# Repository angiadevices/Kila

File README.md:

**!!THIS IS CURRENTLY ENTIRELY UNTESTED!!**

**TODO:** Test PCB design.
Make a better PCB layout because this one is just a complete mess. But if it works...?

## Kila

Kila | किला: Fort/Castle

A Eurorack adaptation of the [Bastl Kastle](https://bastl-instruments.com/instruments/kastle).

This is almost entirely based specifically on the [Sluisbrinkie Kepler](https://github.com/niektb/sluisbrinkie-eurorack-published/tree/main/Sluisbrinkie%20Kepler). There were no hardware files available so I decided to venture into laying out my own.

14HP</br>
Eschews the switches of the original for purely potentiometers and mono jacks.</br>
Includes header for power via external +5VDC source.

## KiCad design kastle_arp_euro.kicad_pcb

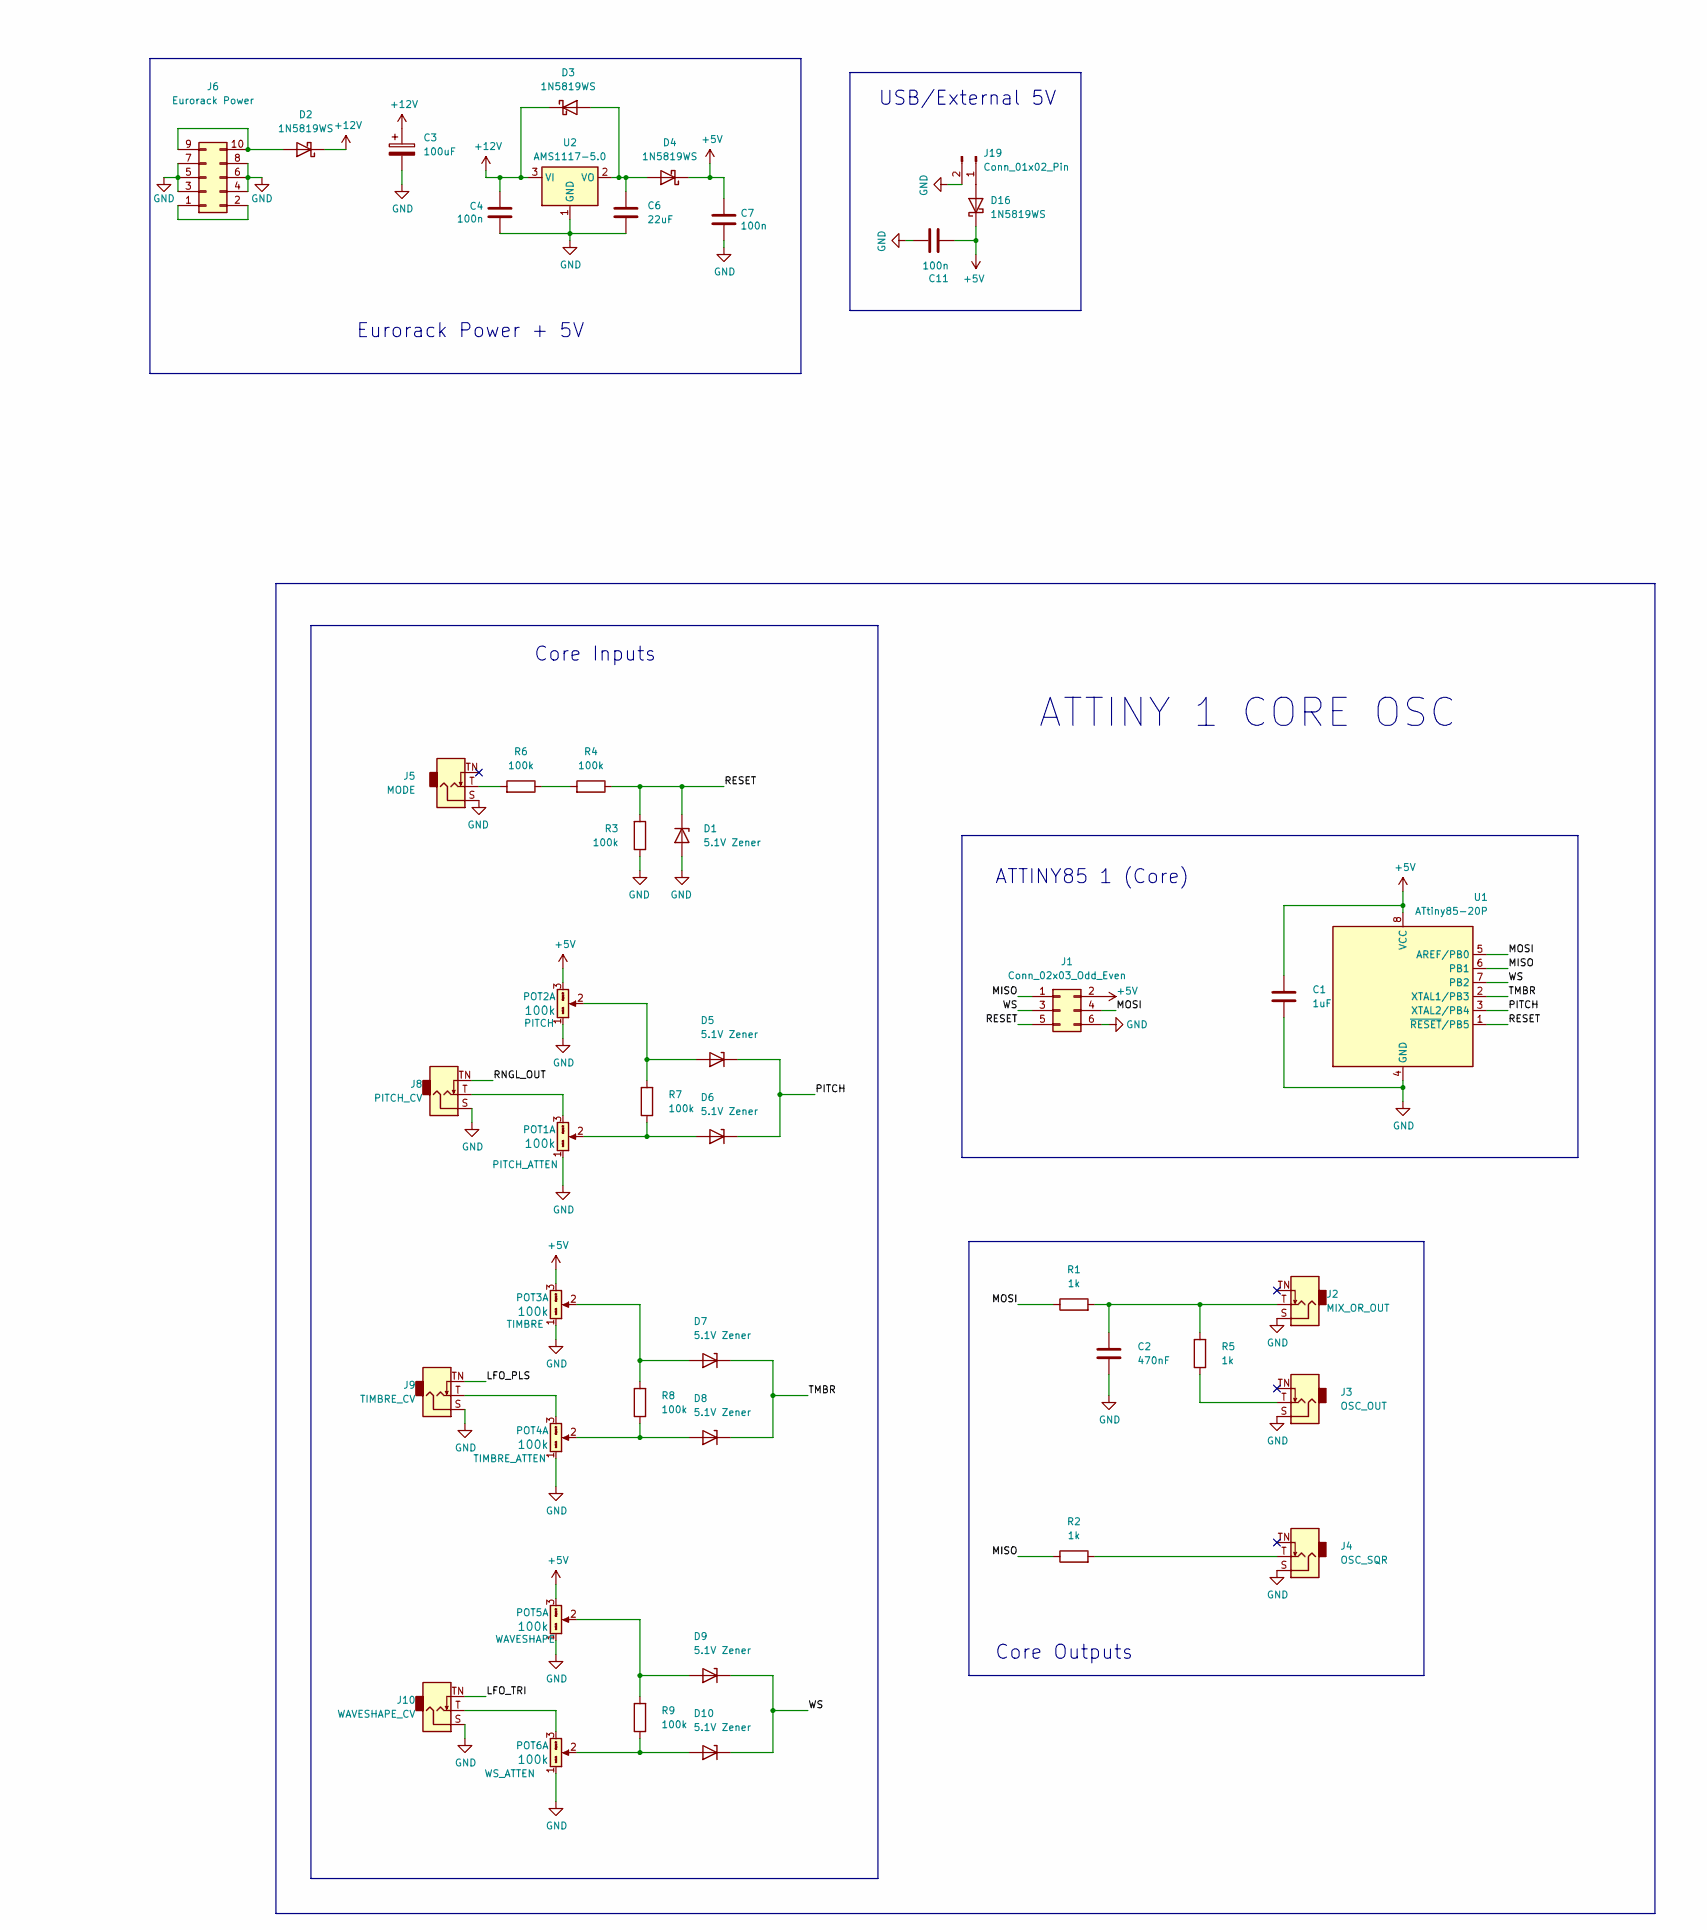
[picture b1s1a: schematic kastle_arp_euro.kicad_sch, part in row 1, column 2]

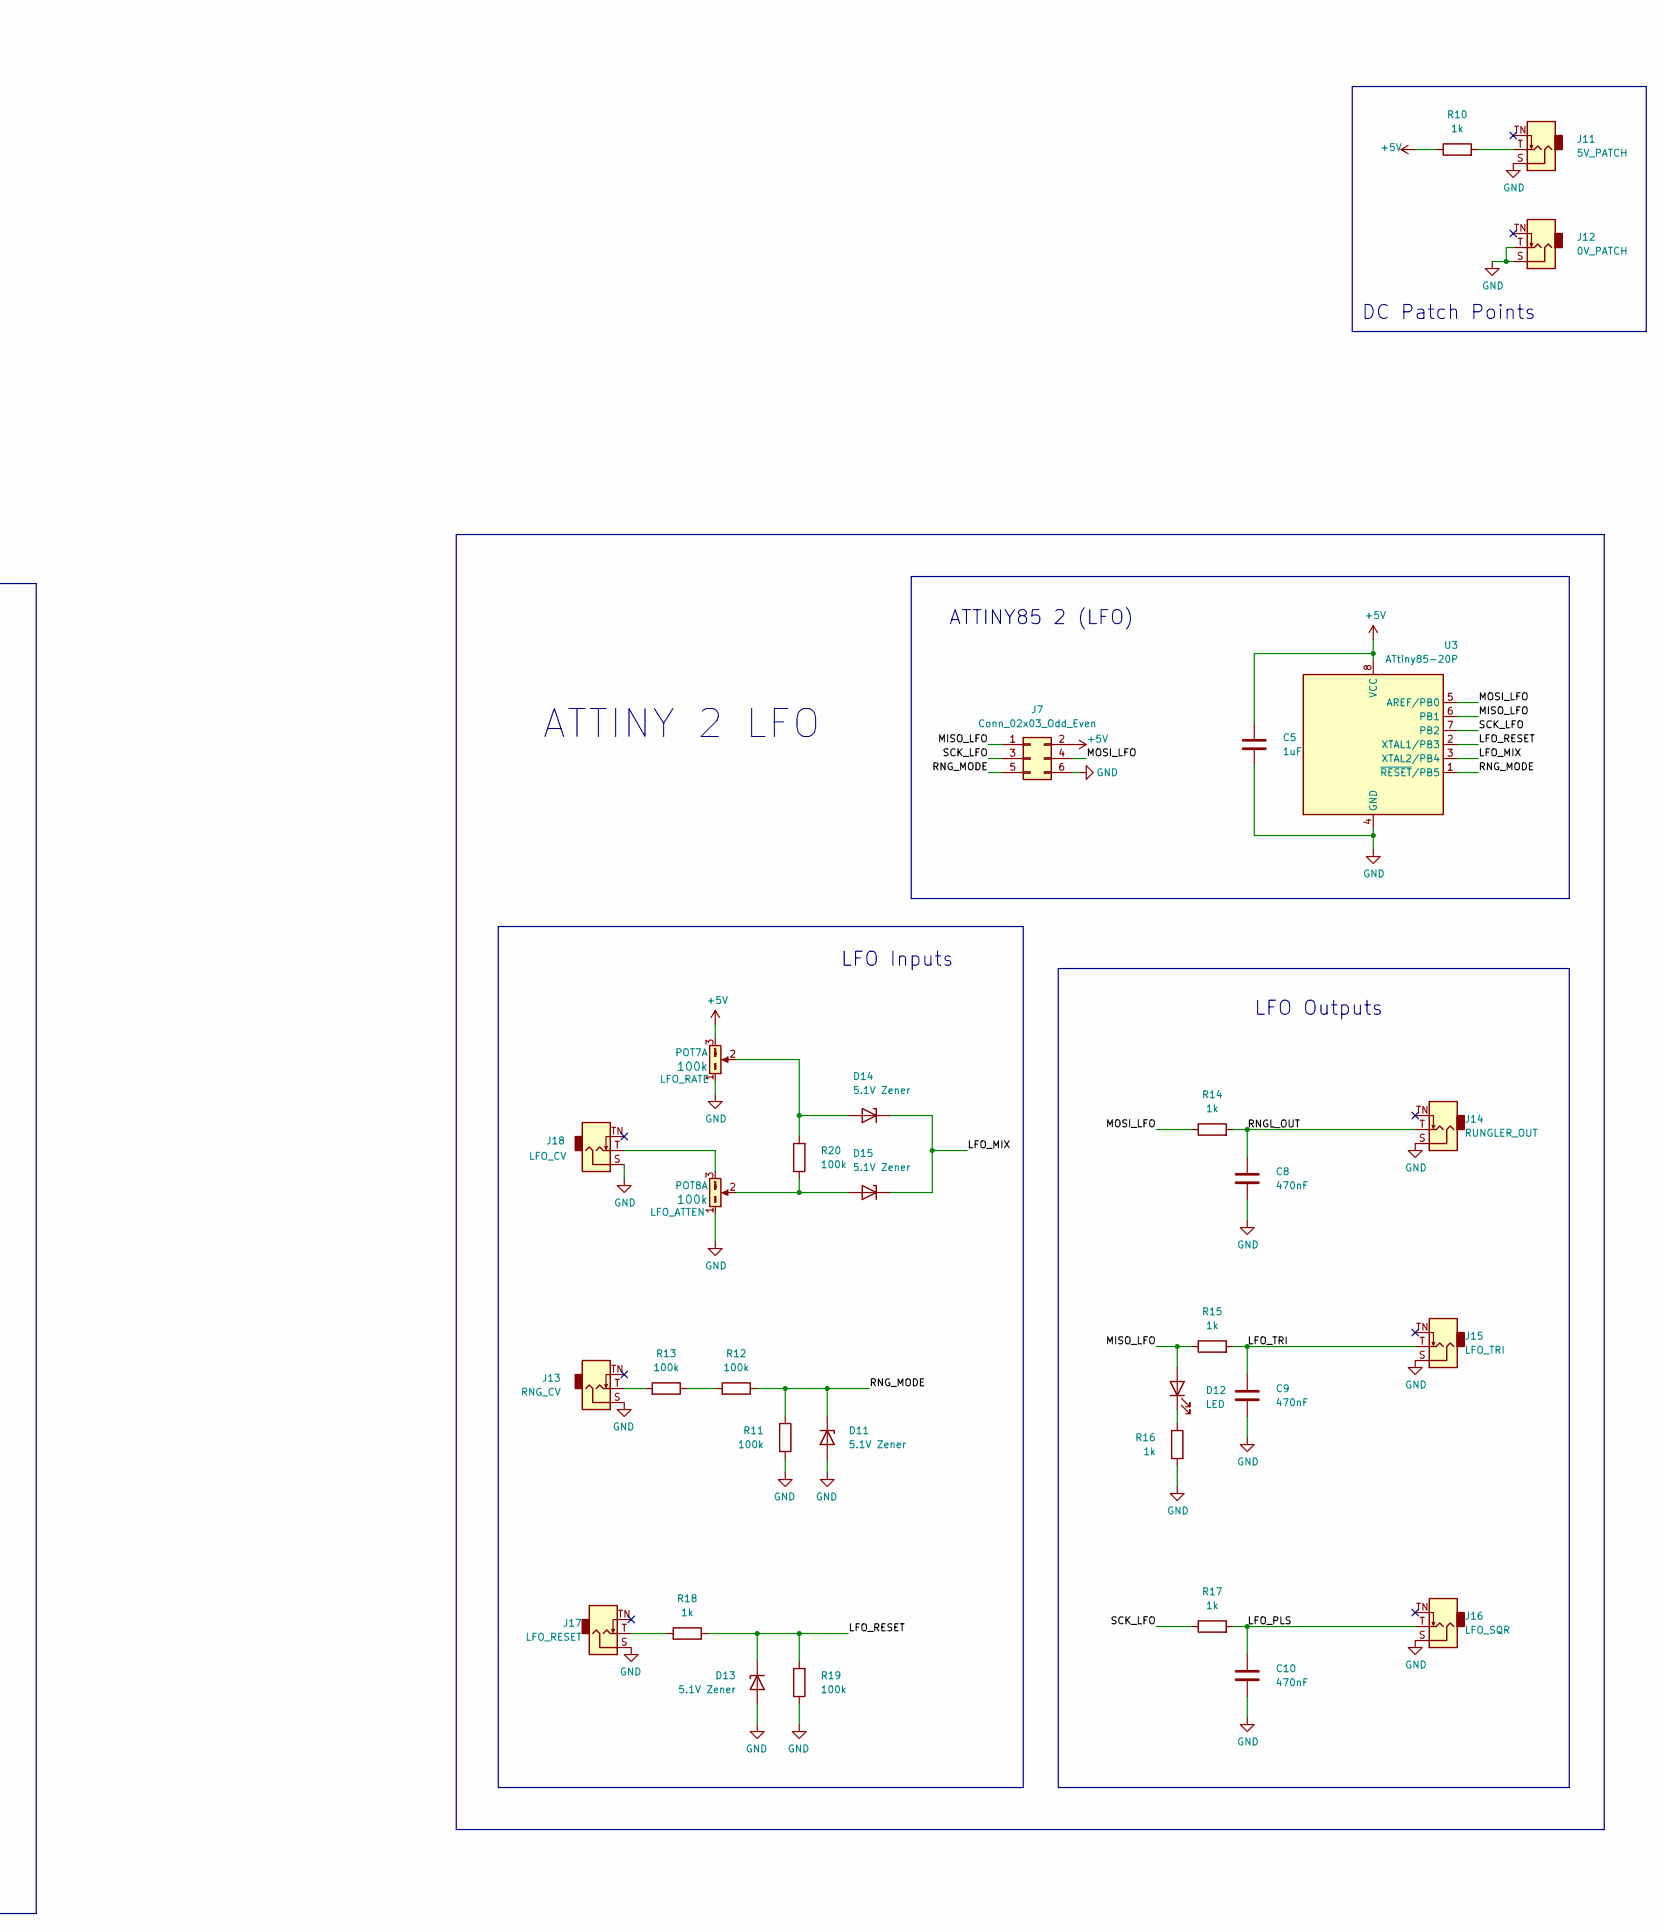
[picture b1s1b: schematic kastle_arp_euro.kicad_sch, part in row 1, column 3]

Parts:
C1, C5: 1uF; C_0805_2012Metric_Pad1.18x1.45mm_HandSolder
C2, C8, C9, C10: 470nF; C_0805_2012Metric_Pad1.18x1.45mm_HandSolder
C3: 100uF; CP_Radial_D6.3mm_P2.50mm
C4, C7, C11: 100n; C_0805_2012Metric_Pad1.18x1.45mm_HandSolder
C6: 22uF; C_1206_3216Metric_Pad1.33x1.80mm_HandSolder
D1, D5, D6, D7, D8, D9, D10, D11, D13, D14, D15: 5.1V Zener; D_MiniMELF_Handsoldering
D2, D3, D4, D16: 1N5819WS; D_SOD-323_HandSoldering
D12: LED; LED_D3.0mm
J1, J7: Conn_02x03_Odd_Even; PinHeader_2x03_P2.54mm_Vertical
J2: MIX_OR_OUT; Jack_3.5mm_QingPu_WQP-PJ398SM_Vertical_CircularHoles
J3: OSC_OUT; Jack_3.5mm_QingPu_WQP-PJ398SM_Vertical_CircularHoles
J4: OSC_SQR; Jack_3.5mm_QingPu_WQP-PJ398SM_Vertical_CircularHoles
J5: MODE; Jack_3.5mm_QingPu_WQP-PJ398SM_Vertical_CircularHoles
J6: Eurorack Power; IDC-Header_2x05_P2.54mm_Vertical
J8: PITCH_CV; Jack_3.5mm_QingPu_WQP-PJ398SM_Vertical_CircularHoles
J9: TIMBRE_CV; Jack_3.5mm_QingPu_WQP-PJ398SM_Vertical_CircularHoles
J10: WAVESHAPE_CV; Jack_3.5mm_QingPu_WQP-PJ398SM_Vertical_CircularHoles
J11: 5V_PATCH; Jack_3.5mm_QingPu_WQP-PJ398SM_Vertical_CircularHoles
J12: 0V_PATCH; Jack_3.5mm_QingPu_WQP-PJ398SM_Vertical_CircularHoles
J13: RNG_CV; Jack_3.5mm_QingPu_WQP-PJ398SM_Vertical_CircularHoles
J14: RUNGLER_OUT; Jack_3.5mm_QingPu_WQP-PJ398SM_Vertical_CircularHoles
J15: LFO_TRI; Jack_3.5mm_QingPu_WQP-PJ398SM_Vertical_CircularHoles
J16: LFO_SQR; Jack_3.5mm_QingPu_WQP-PJ398SM_Vertical_CircularHoles
J17: LFO_RESET; Jack_3.5mm_QingPu_WQP-PJ398SM_Vertical_CircularHoles
J18: LFO_CV; Jack_3.5mm_QingPu_WQP-PJ398SM_Vertical_CircularHoles
J19: Conn_01x02_Pin; JST_EH_B2B-EH-A_1x02_P2.50mm_Vertical
POT1: PITCH_ATTEN; Potentiometer_Alpha_RD901F-40-00D_Single_Vertical; Part Number RV16AF-4A-15FW-B100K-3
POT2: PITCH; Potentiometer_Alpha_RD901F-40-00D_Single_Vertical; Part Number RV16AF-4A-15FW-B100K-3
POT3: TIMBRE; Potentiometer_Alpha_RD901F-40-00D_Single_Vertical; Part Number RV16AF-4A-15FW-B100K-3
POT4: TIMBRE_ATTEN; Potentiometer_Alpha_RD901F-40-00D_Single_Vertical; Part Number RV16AF-4A-15FW-B100K-3
POT5: WAVESHAPE; Potentiometer_Alpha_RD901F-40-00D_Single_Vertical; Part Number RV16AF-4A-15FW-B100K-3
POT6: WS_ATTEN; Potentiometer_Alpha_RD901F-40-00D_Single_Vertical; Part Number RV16AF-4A-15FW-B100K-3
POT7: LFO_RATE; Potentiometer_Alpha_RD901F-40-00D_Single_Vertical; Part Number RV16AF-4A-15FW-B100K-3
POT8: LFO_ATTEN; Potentiometer_Alpha_RD901F-40-00D_Single_Vertical; Part Number RV16AF-4A-15FW-B100K-3
R1, R2, R5, R10, R14, R15, R16, R17, R18: 1k; R_0805_2012Metric_Pad1.20x1.40mm_HandSolder
R3, R4, R6, R7, R8, R9, R11, R12, R13, R19, R20: 100k; R_0805_2012Metric_Pad1.20x1.40mm_HandSolder
U1, U3: ATtiny85-20P; SOIC-8_3.9x4.9mm_P1.27mm
U2: AMS1117-5.0; SOT-223-3_TabPin2

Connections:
+5V: C1.1, C5.1, C7.1, C11.1, D4.1 (K), D16.1 (K), J1.2, J7.2, POT2.3 (Right), POT3.3 (Right), POT5.3 (Right), POT7.3 (Right), R10.1, U1.8 (VCC), U3.8 (VCC)
+12V: C3.1, C4.1, D2.1 (K), D3.1 (K), U2.3 (VI)
/LFO_MIX: D14.1 (K), D15.1 (K), U3.3 (XTAL2/PB4)
/LFO_PLS: C10.1, J9.TN, J16.T, R17.2
/LFO_RESET: D13.1 (K), R18.1, R19.2, U3.2 (XTAL1/PB3)
/LFO_TRI: C9.1, J10.TN, J15.T, R15.2
/MISO: J1.1, R2.1, U1.6 (PB1)
/MISO_LFO: D12.2 (A), J7.1, R15.1, U3.6 (PB1)
/MOSI: J1.4, R1.1, U1.5 (AREF/PB0)
/MOSI_LFO: J7.4, R14.1, U3.5 (AREF/PB0)
/PITCH: D5.1 (K), D6.1 (K), U1.3 (XTAL2/PB4)
/RESET: D1.1 (K), J1.5, R3.2, R4.1, U1.1 (~RESET/PB5)
/RNGL_OUT: C8.1, J8.TN, J14.T, R14.2
/RNG_MODE: D11.1 (K), J7.5, R11.2, R12.1, U3.1 (~RESET/PB5)
/SCK_LFO: J7.3, R17.1, U3.7 (PB2)
/TMBR: D7.1 (K), D8.1 (K), U1.2 (XTAL1/PB3)
/WS: D9.1 (K), D10.1 (K), J1.3, U1.7 (PB2)
GND: C1.2, C2.2, C3.2, C4.2, C5.2, C6.2, C7.2, C8.2, C9.2, C10.2, C11.2, D1.2 (A), D11.2 (A), D13.2 (A), J1.6, J2.S, J3.S, J4.S, J5.S, J6.3, J6.4, J6.5, J6.6, J6.7, J6.8, J7.6, J8.S, J9.S, J10.S, J11.S, J12.S, J12.T, J13.S, J14.S, J15.S, J16.S, J17.S, J18.S, J19.2, POT1.1 (Left), POT2.1 (Left), POT3.1 (Left), POT4.1 (Left), POT5.1 (Left), POT6.1 (Left), POT7.1 (Left), POT8.1 (Left), R3.1, R11.1, R16.2, R19.1, U1.4 (GND), U2.1 (GND), U3.4 (GND)
unnamed: C2.1, J2.T, R1.2, R5.2
unnamed: D2.2 (A), J6.9, J6.10
unnamed: C6.1, D3.2 (A), D4.2 (A), U2.2 (VO)
unnamed: D5.2 (A), POT2.2 (Center), R7.2
unnamed: D6.2 (A), POT1.2 (Center), R7.1
unnamed: D7.2 (A), POT3.2 (Center), R8.2
unnamed: D8.2 (A), POT4.2 (Center), R8.1
unnamed: D9.2 (A), POT5.2 (Center), R9.2
unnamed: D10.2 (A), POT6.2 (Center), R9.1
unnamed: D12.1 (K), R16.1
unnamed: D14.2 (A), POT7.2 (Center), R20.2
unnamed: D15.2 (A), POT8.2 (Center), R20.1
unnamed: D16.2 (A), J19.1
unnamed: J3.T, R5.1
unnamed: J4.T, R2.2
unnamed: J5.T, R6.2
unnamed: J6.1, J6.2
unnamed: J11.T, R10.2
unnamed: J13.T, R13.2
unnamed: J17.T, R18.2
unnamed: J8.T, POT1.3 (Right)
unnamed: J9.T, POT4.3 (Right)
unnamed: J10.T, POT6.3 (Right)
unnamed: J18.T, POT8.3 (Right)
unnamed: R4.2, R6.1
unnamed: R12.2, R13.1

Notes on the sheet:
ATTINY 1 CORE OSC
USB/External 5V
Core Inputs
ATTINY85 2 (LFO)
ATTINY 2 LFO
LFO Inputs
Core Outputs
DC Patch Points
Eurorack Power + 5V
LFO Outputs
ATTINY85 1 (Core)

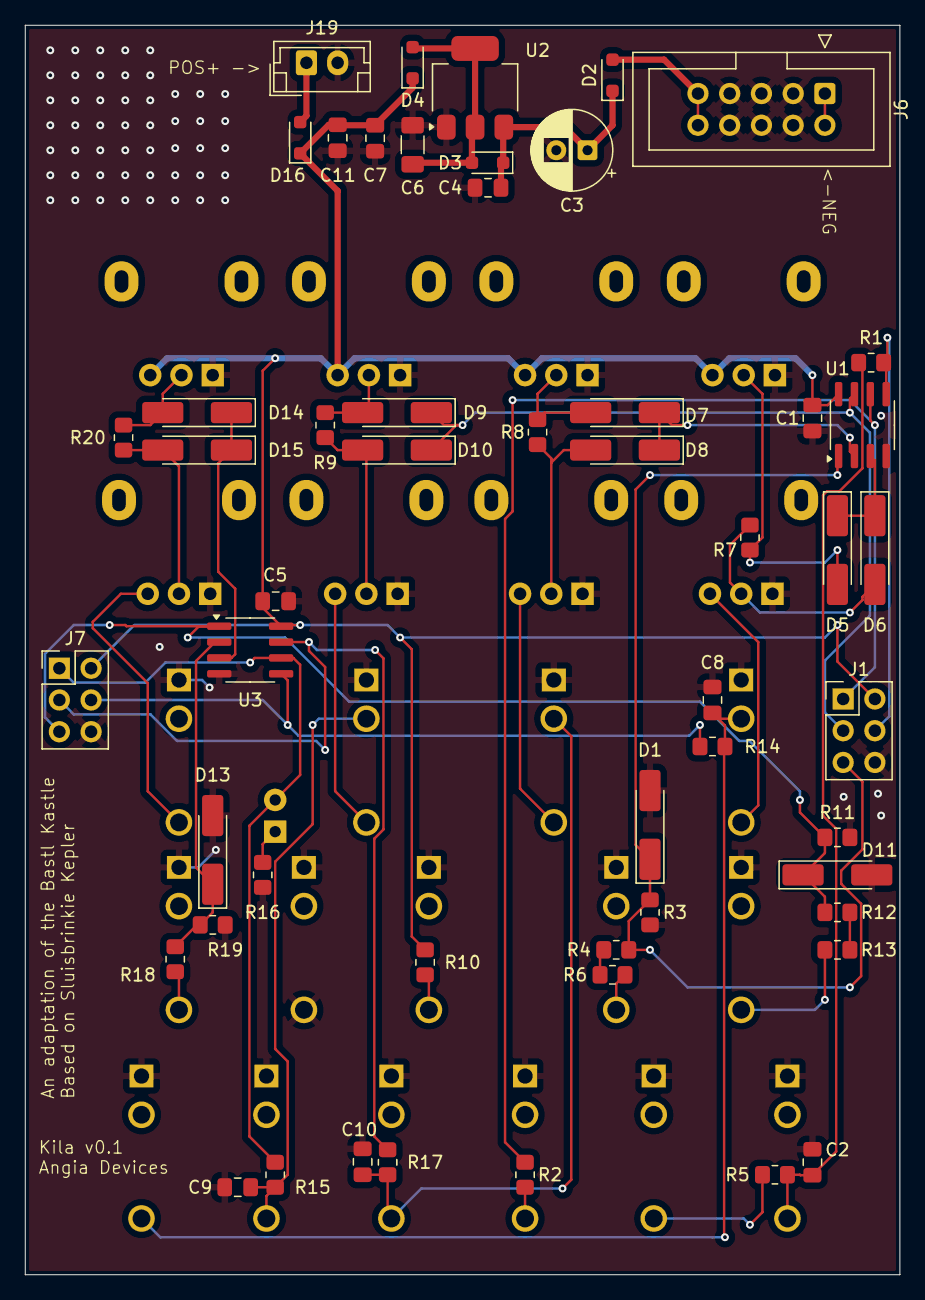
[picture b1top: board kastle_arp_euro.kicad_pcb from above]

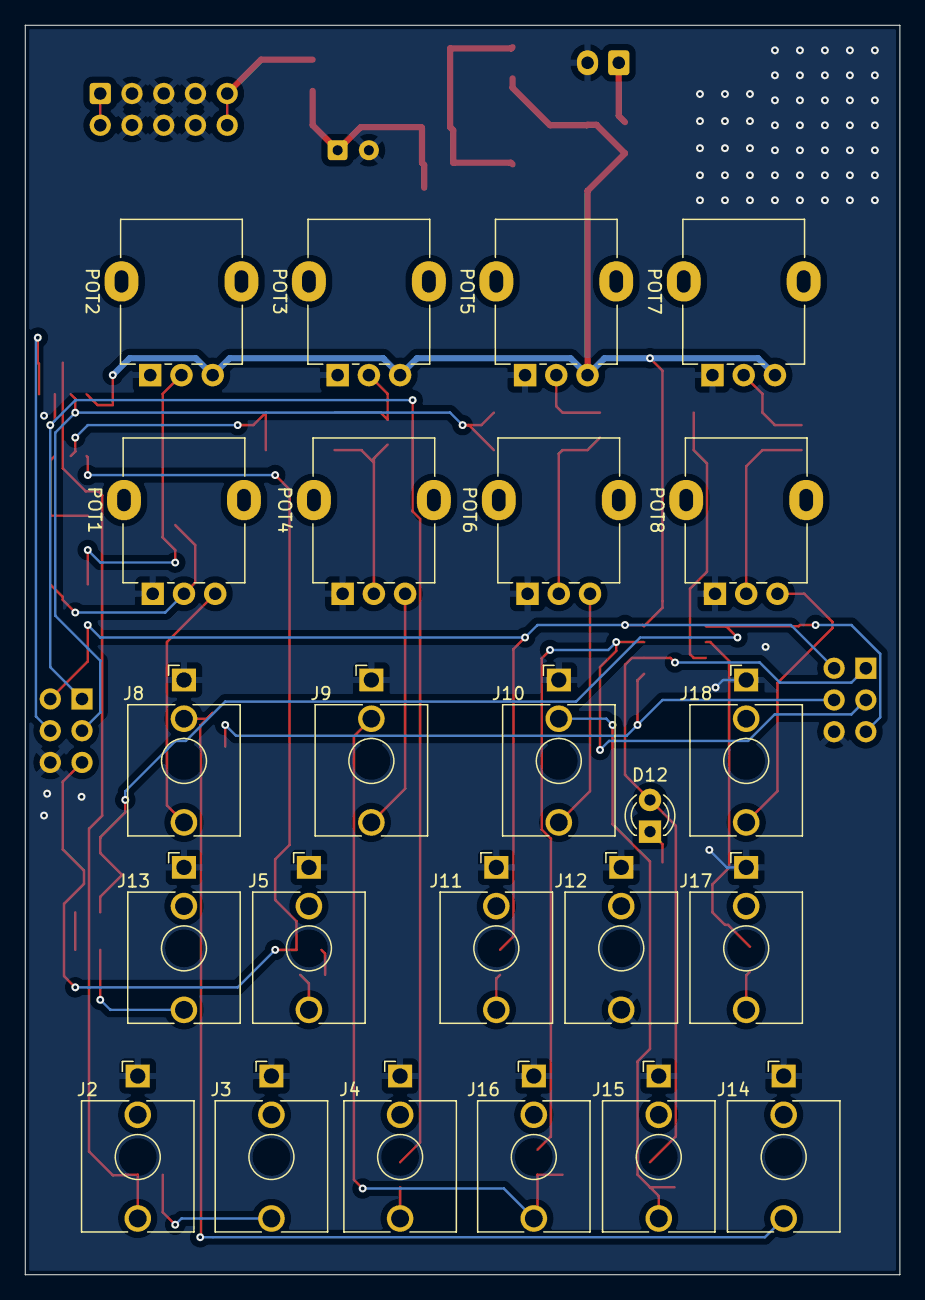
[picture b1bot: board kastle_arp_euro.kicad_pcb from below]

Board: 2 copper layers, 70.0 x 100.0 mm, 77 parts (24 on the bottom side), 44 nets.
